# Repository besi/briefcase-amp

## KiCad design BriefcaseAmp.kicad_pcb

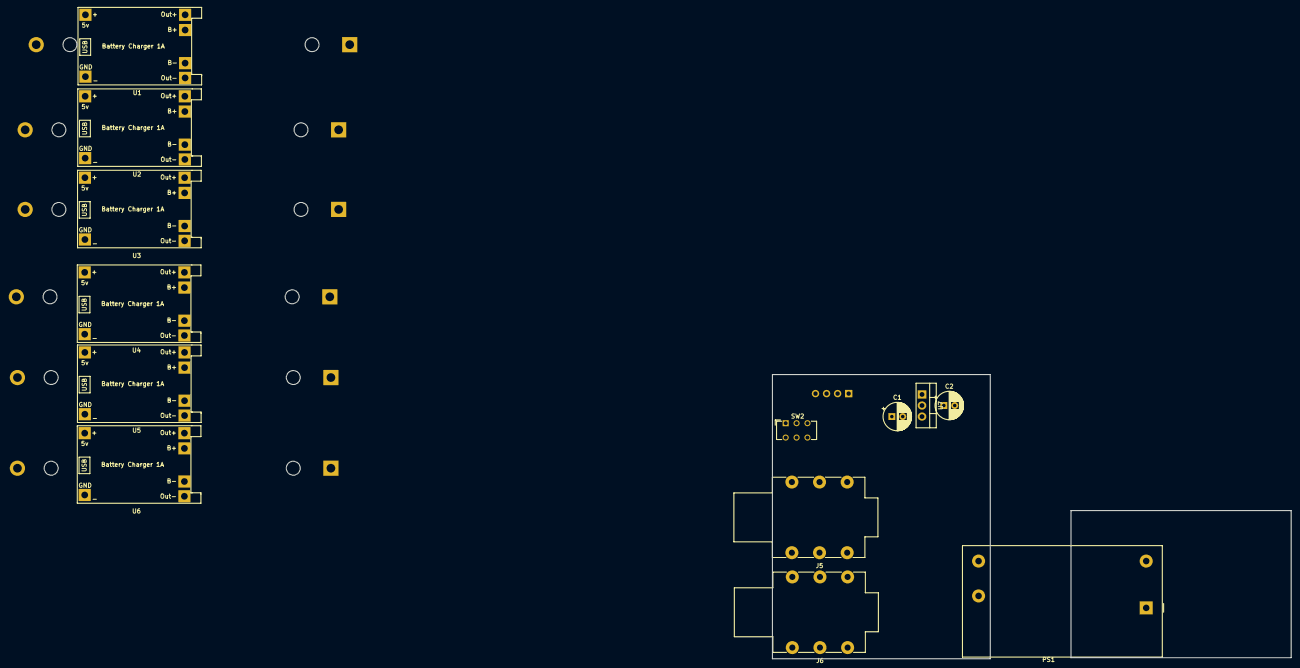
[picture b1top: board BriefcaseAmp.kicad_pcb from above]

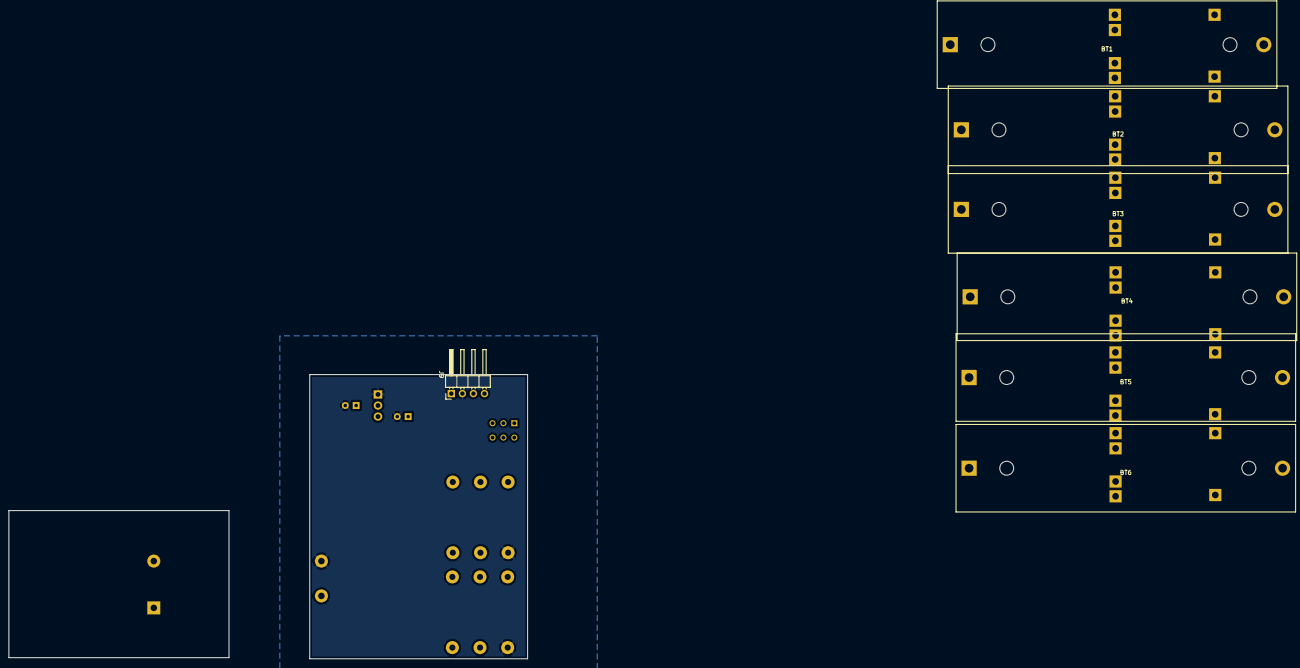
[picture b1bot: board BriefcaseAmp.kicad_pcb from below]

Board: 2 copper layers, 119.1 x 65.3 mm, 20 parts (7 on the bottom side), 22 nets, no tracks yet.

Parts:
BT1, BT2, BT3, BT4, BT5, BT6: Battery_Cell; BatteryHolder_MPD_BH-18650-PC2
C1, C2: C_Polarized; CP_Radial_D6.3mm_P2.50mm
J5: Left; Jack_6.35mm_Neutrik_NMJ6HHD2_Horizontal
J6: Right; Jack_6.35mm_Neutrik_NMJ6HHD2_Horizontal
J9: Power Inlet; PinHeader_1x04_P2.54mm_Horizontal
PS1: IRM-05-5; Converter_ACDC_MeanWell_IRM-05-xx_THT
SW2: Enable Amp; SW_CuK_JS202011CQN_DPDT_Straight
U1, U2, U3, U4, U5, U6: TP4056
U7: LD1086V33-DG; TO-220-3_Vertical

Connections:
+3V3: C2.1, U7.2 (OUT)
+12V: J9.4, SW2.2 (B)
-12V: J9.1, SW2.5 (B)
GND: C1.2, C2.2, J5.S, J6.S, J9.2, PS1.3 (-Vo), U7.1 (ADJ/GND)
GNDA: U3.4 (OUT-), U4.3 (OUT+)
unnamed: BT1.1 (+), U1.5 (B+)
unnamed: BT1.2 (-), U1.6 (B-)
unnamed: BT2.1 (+), U2.5 (B+)
unnamed: BT2.2 (-), U2.6 (B-)
unnamed: BT3.1 (+), U3.5 (B+)
unnamed: BT3.2 (-), U3.6 (B-)
unnamed: BT4.1 (+), U4.5 (B+)
unnamed: BT4.2 (-), U4.6 (B-)
unnamed: BT5.1 (+), U5.5 (B+)
unnamed: BT5.2 (-), U5.6 (B-)
unnamed: BT6.1 (+), U6.5 (B+)
unnamed: BT6.2 (-), U6.6 (B-)
unnamed: C1.1, U7.3 (IN)
unnamed: U2.4 (OUT-), U3.3 (OUT+)
unnamed: U1.4 (OUT-), U2.3 (OUT+)
unnamed: U4.4 (OUT-), U5.3 (OUT+)
unnamed: U5.4 (OUT-), U6.3 (OUT+)

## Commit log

2022-12-27 Added project
2023-01-03 Add tp4056 module
2023-01-03 Add main components
2023-01-03 Add a readme
